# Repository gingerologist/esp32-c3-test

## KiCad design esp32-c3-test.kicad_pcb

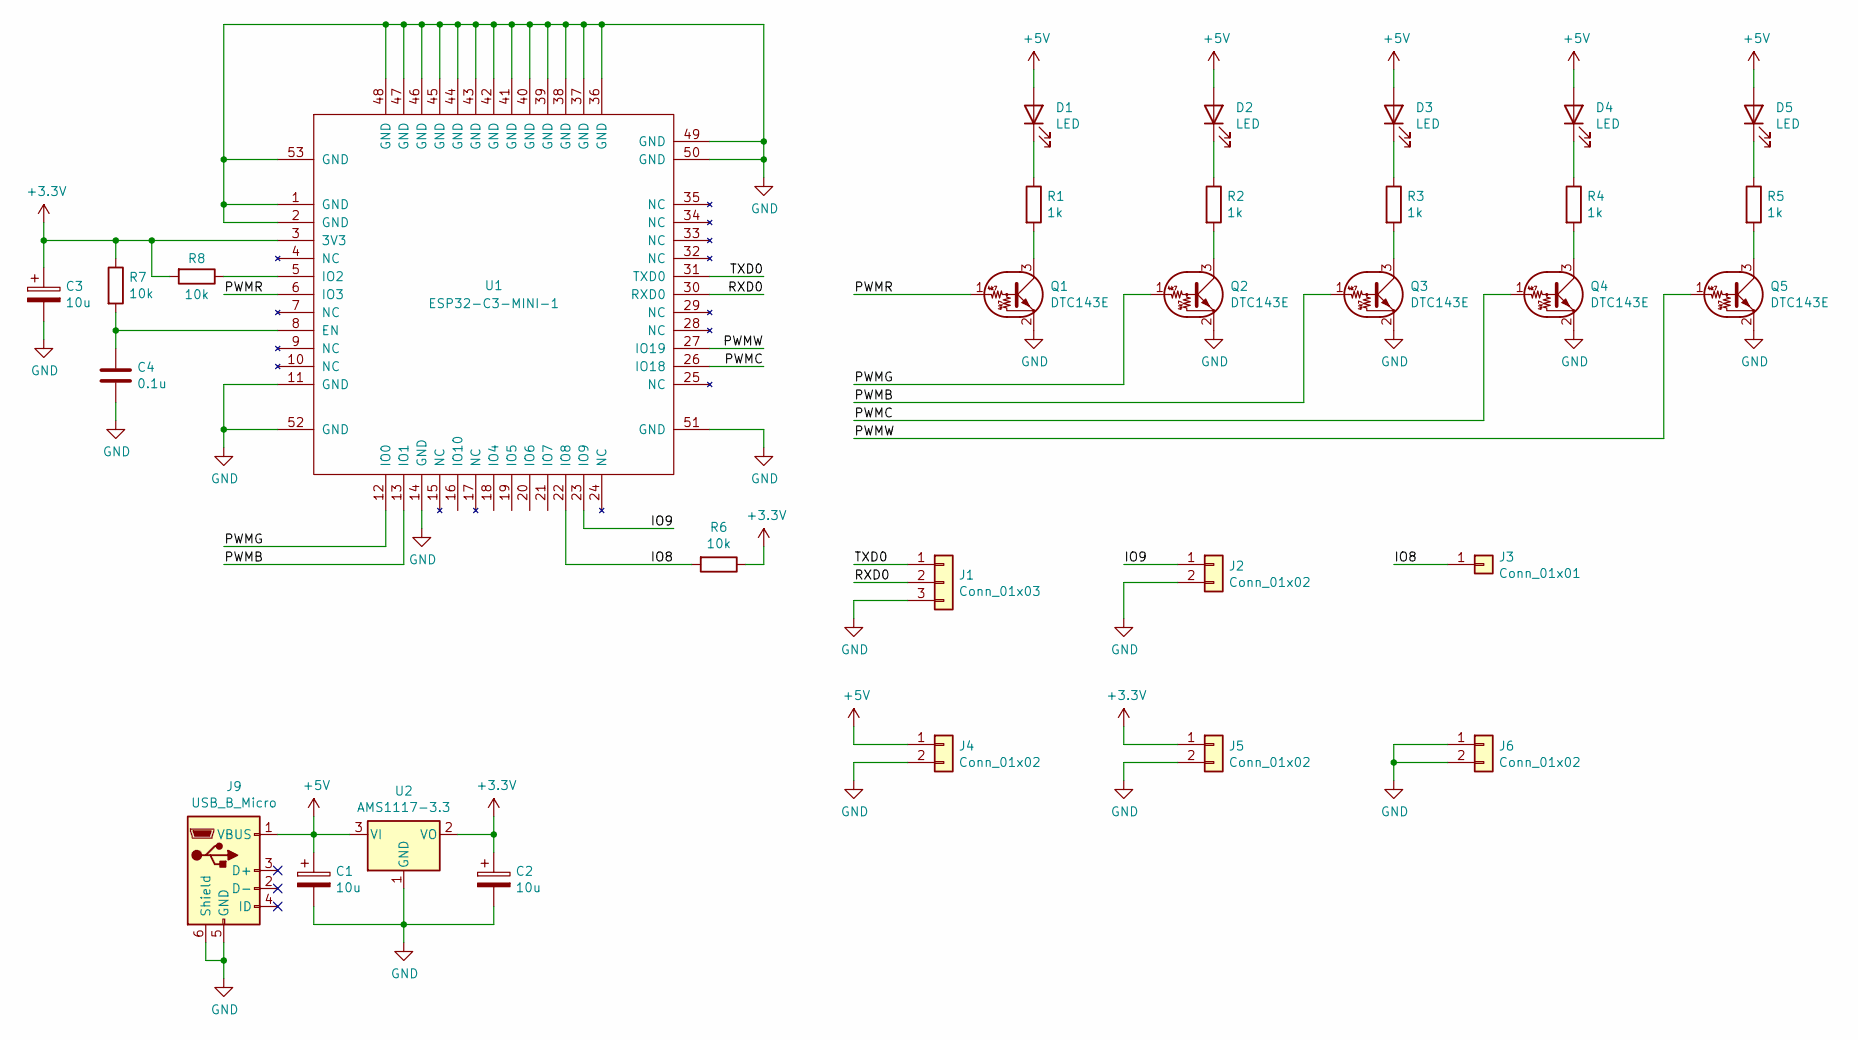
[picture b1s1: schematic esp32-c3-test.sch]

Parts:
C1, C2, C3: 10u; CP_EIA-3528-21_Kemet-B_Pad1.50x2.35mm_HandSolder
C4: 0.1u; C_0603_1608Metric_Pad1.08x0.95mm_HandSolder
D1, D2, D3, D4, D5: LED; LED_0805_2012Metric_Castellated
J1: Conn_01x03; PinHeader_1x03_P2.54mm_Vert
J2, J4, J5, J6: Conn_01x02; PinHeader_1x02_P2.54mm_Vert
J3: Conn_01x01; PinHeader_1x01_P2.54mm_Vertical
J9: USB_B_Micro; USB_Micro-B_Molex-105017-0001
Q1, Q2, Q3, Q4, Q5: DTC143E; SOT-23
R1, R2, R3, R4, R5: 1k; R_0603_1608Metric_Pad0.98x0.95mm_HandSolder
R6, R7, R8: 10k; R_0603_1608Metric_Pad0.98x0.95mm_HandSolder
U1: ESP32-C3-MINI-1
U2: AMS1117-3.3; SOT-223-3_TabPin2

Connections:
+3V3: C2.1, C3.1, J5.1, R6.1, R7.1, R8.2, U1.3 (3V3), U2.2 (VO)
+5V: C1.1, D1.2 (A), D2.2 (A), D3.2 (A), D4.2 (A), D5.2 (A), J4.1, J9.1 (VBUS), U2.3 (VI)
/IO8: J3.1, R6.2, U1.22 (IO8)
/IO9: J2.1, U1.23 (IO9)
/PWMB: Q3.1 (B), U1.13 (IO1)
/PWMC: Q4.1 (B), U1.26 (IO18)
/PWMG: Q2.1 (B), U1.12 (IO0)
/PWMR: Q1.1 (B), U1.6 (IO3)
/PWMW: Q5.1 (B), U1.27 (IO19)
/RXD0: J1.2, U1.30 (RXD0)
/TXD0: J1.1, U1.31 (TXD0)
GND: C1.2, C2.2, C3.2, C4.2, J1.3, J2.2, J4.2, J5.2, J6.1, J6.2, J9.5 (GND), J9.6 (Shield), Q1.2 (E), Q2.2 (E), Q3.2 (E), Q4.2 (E), Q5.2 (E), U1.1 (GND), U1.2 (GND), U1.11 (GND), U1.14 (GND), U1.36 (GND), U1.37 (GND), U1.38 (GND), U1.39 (GND), U1.40 (GND), U1.41 (GND), U1.42 (GND), U1.43 (GND), U1.44 (GND), U1.45 (GND), U1.46 (GND), U1.47 (GND), U1.48 (GND), U1.49 (GND), U1.50 (GND), U1.51 (GND), U1.52 (GND), U1.53 (GND), U2.1 (GND)
unnamed: C4.1, R7.2, U1.8 (EN)
unnamed: D1.1 (K), R1.1
unnamed: D2.1 (K), R2.1
unnamed: D3.1 (K), R3.1
unnamed: D4.1 (K), R4.1
unnamed: D5.1 (K), R5.1
unnamed: Q1.3 (C), R1.2
unnamed: Q2.3 (C), R2.2
unnamed: Q3.3 (C), R3.2
unnamed: Q4.3 (C), R4.2
unnamed: Q5.3 (C), R5.2
unnamed: R8.1, U1.5 (IO2)

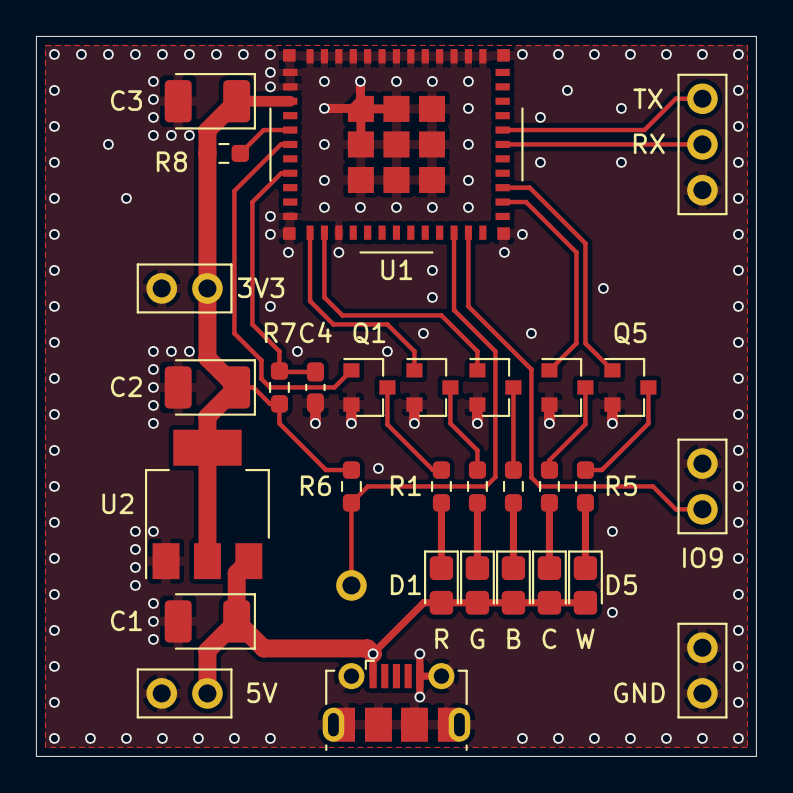
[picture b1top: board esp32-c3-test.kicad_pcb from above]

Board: 2 copper layers, 40.0 x 40.0 mm, 31 parts (0 on the bottom side), 24 nets.

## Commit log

2021-11-08 almost ok
2021-11-08 add klc doc
2021-11-08 1. change c5 to c4 2. modify silkscreen of esp32-c3-mini-1 footprint to avoid via 3. move a few vias
2021-11-08 update copper fill and generate manufacturing files.
2021-11-08 add README.md in manufacturing directory, with two images.
2021-11-08 add readme and schematic in pdf format
2021-11-22 export position file for smt
    ref: http://club.szlcsc.com/article/auther_2386_1_223282.html
2021-11-22 1. unignore .csv file 2. add position file in csv format
2021-11-23 1. modify esp32-c3-mini-1 module footprint, marked as smd 2. update pcb file 3. update exported position file
